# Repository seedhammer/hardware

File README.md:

# SeedHammer II hardware

This repository contains the design files for the [SeedHammer II](https://seedhammer.com)
machine.

## PCB

The schematic and PCB are in [KiCad](https://kicad.org) format. 

Generate production files (gerber, BOM, CPL) with the Go script:
```sh
$ cd pcb
$ PATH=$PATH:/path/to/kicad-cli go run .
```

Production boards are manufactured by [JLCPCB](https://jlcpcb.com) with the following
settings:

 - Surface Finish: ENIG
 - Material Type: FR4 TG155
 - Stackup: JLC04161H-7628 (impedance controlled)

### LCD

The LCD is a [ER-TFT035IPS-6](https://www.buydisplay.com/3-5-inch-ips-320x480-tft-lcd-display-capacitive-touch-screen)
with capacitive touch from buydisplay.com. The variant with resistive touch is not supported by the firmware.

## CAD

The CAD files for the custom machine parts are in STEP format.

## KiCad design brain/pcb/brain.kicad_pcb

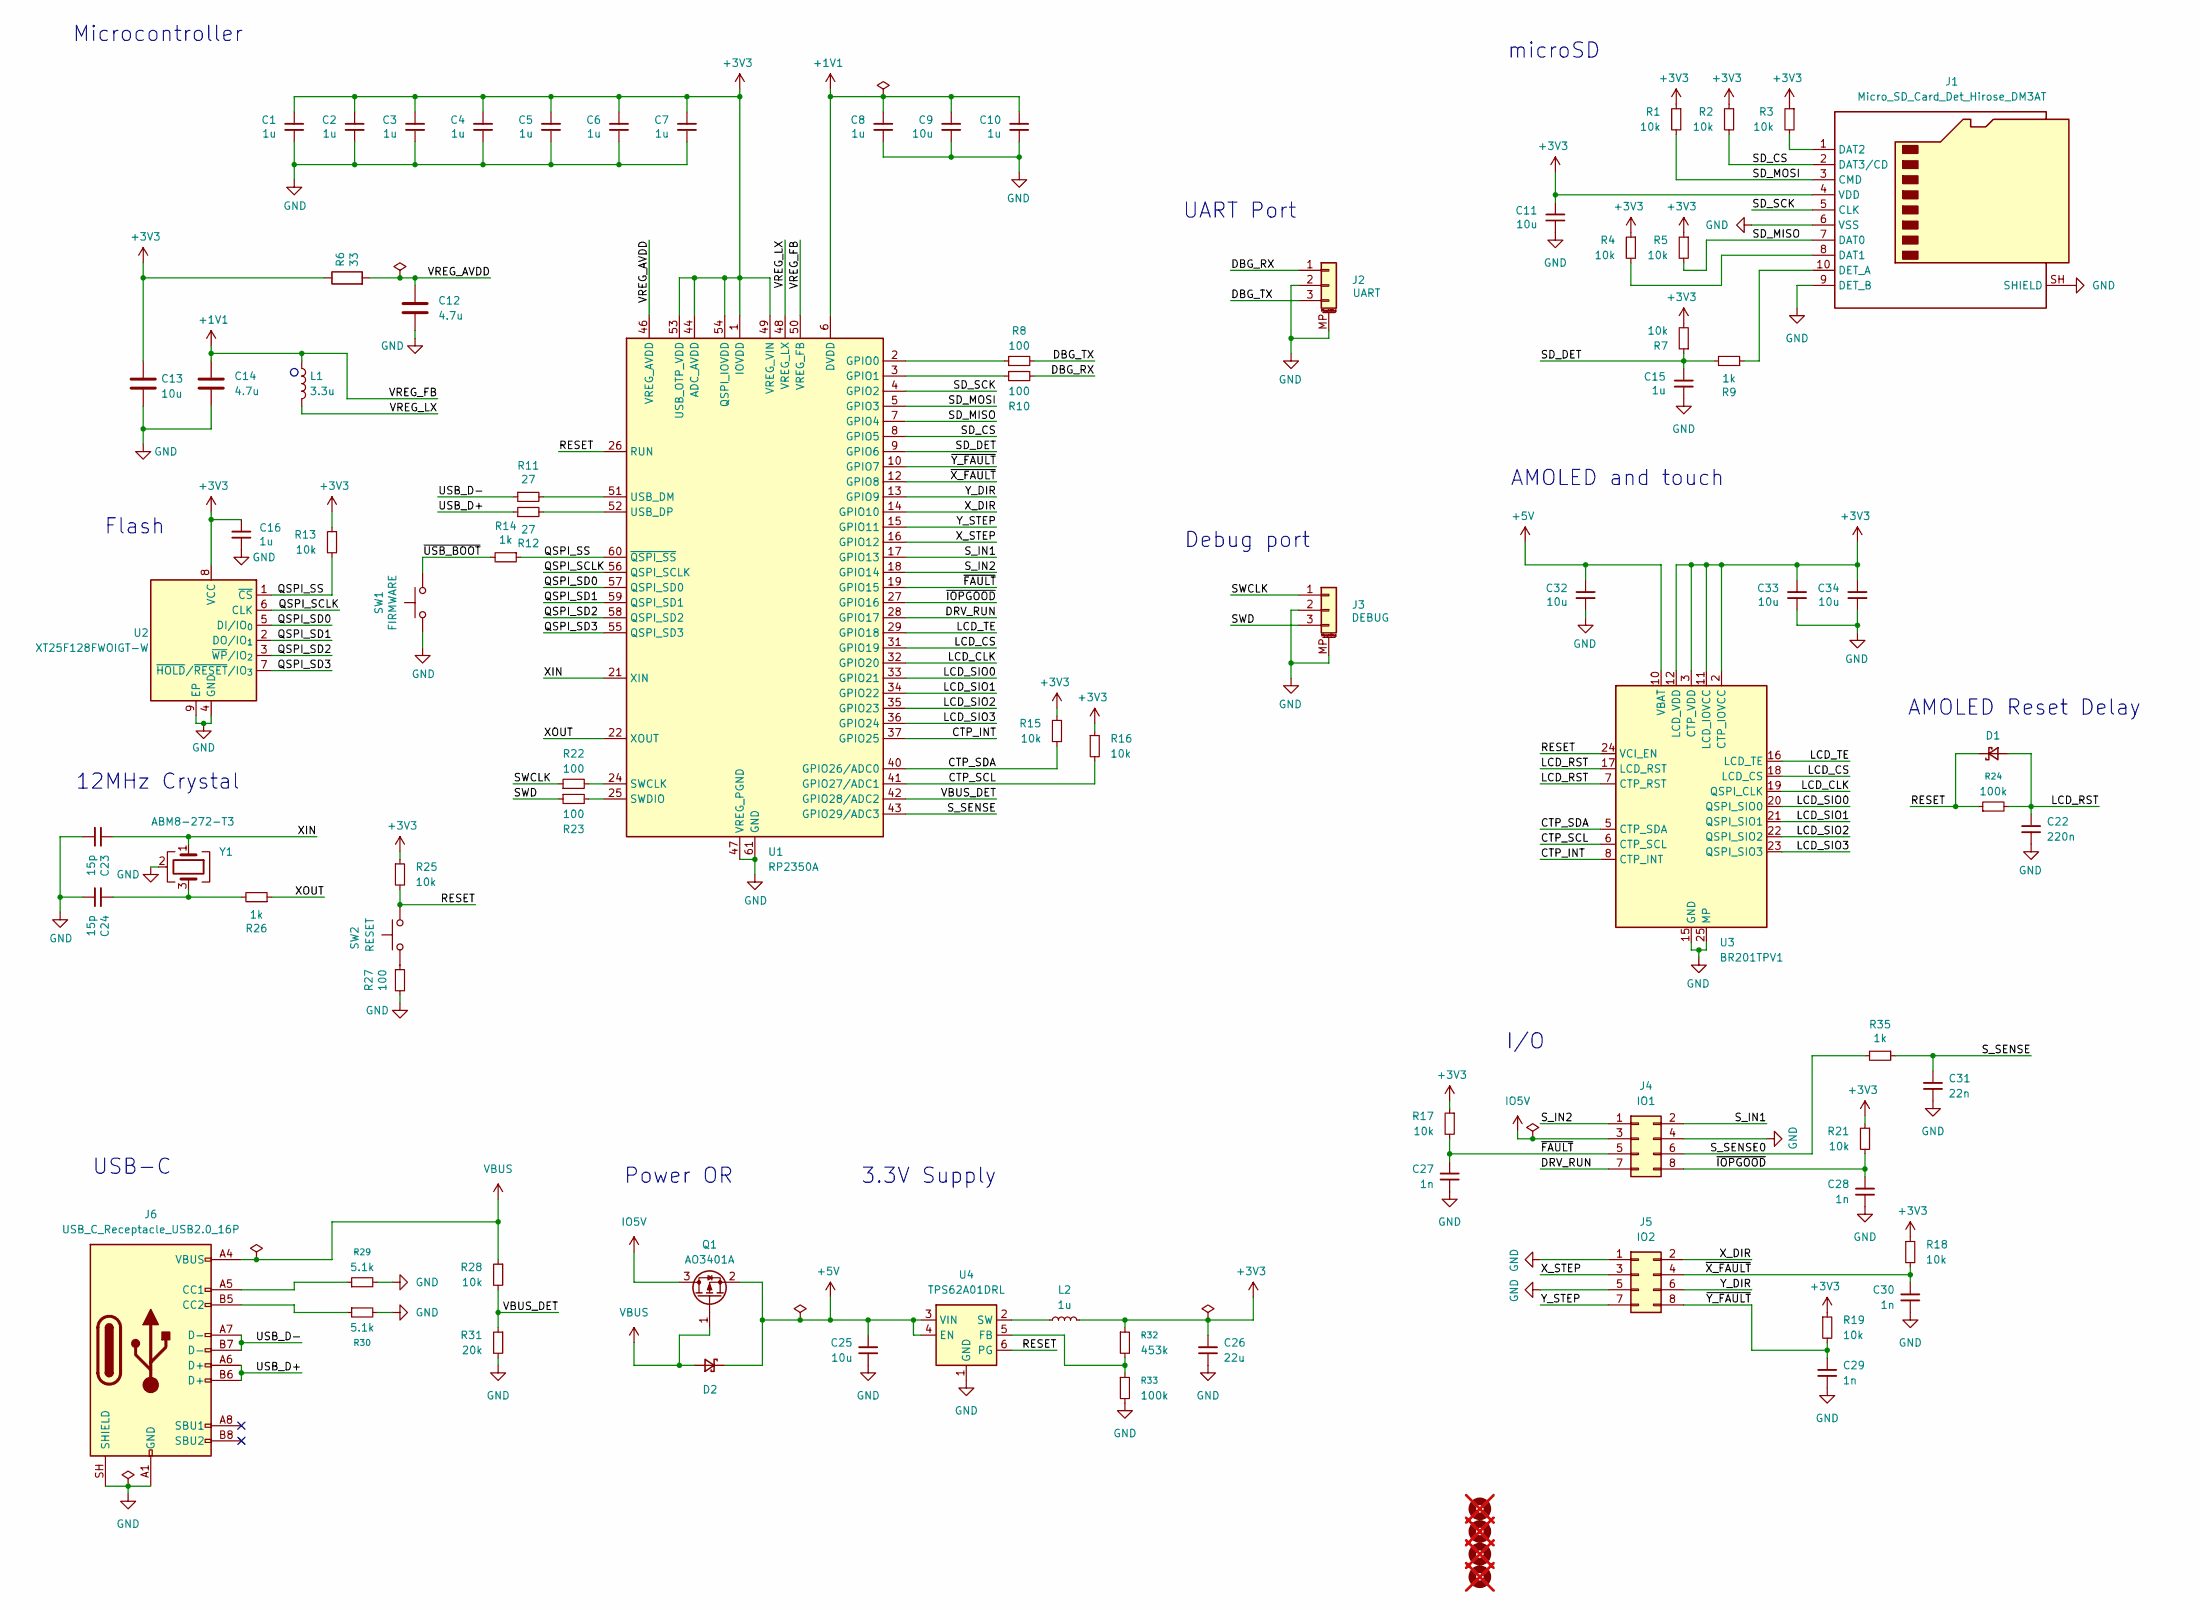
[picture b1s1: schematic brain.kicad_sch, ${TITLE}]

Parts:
C1, C2, C3, C4, C5, C6, C7, C8, C10, C15, C16: 1u; C_0402_1005Metric; LCSC C52923
C9, C11, C32, C33, C34: 10u; C_0402_1005Metric; LCSC C15525
C12: 4.7u; C_0402_1005Metric; LCSC C23733
C13: 10u; C_0402_1005Metric_small_pads; LCSC C15525
C14: 4.7u; C_0402_1005Metric_small_pads; LCSC C23733
C22: 220n; C_0402_1005Metric; LCSC C16772
C23, C24: 15p; C_0402_1005Metric; LCSC C1548
C25: 10u; C_0603_1608Metric; LCSC C96446
C26: 22u; C_0603_1608Metric; LCSC C59461
C27, C28, C29, C30: 1n; C_0402_1005Metric; LCSC C1523
C31: 22n; C_0402_1005Metric; LCSC C1532
D1: D_SOD-523; LCSC C7502700
D2: D_SOD-323; LCSC C191023
H1, H2, H3, H4: MountingHole; MountingHole_2.2mm_M2_DIN965; not fitted
J1: Micro_SD_Card_Det_Hirose_DM3AT; microSD_HC_Hirose_DM3AT-SF-PEJM5; LCSC C114218
J2, J3: WAFER-SH1.0-3PWB; JST_SH_SM03B-SRSS-TB_1x03-1MP_P1.00mm_Horizontal; LCSC C3029342
J4: IO1; Pogo_IO_2x04_P2.5mm
J5: IO2; Pogo_IO_2x04_P2.5mm
J6: USB_C_Receptacle_USB2.0_16P; USB_C_Receptacle_GCT_USB4105-xx-A_16P_TopMnt_Horizontal; LCSC C3020560
L1: 3.3u; L_pol_2016; LCSC C42411119
L2: 1u; L_0603_1608Metric; LCSC C17701610
Q1: AO3401A; SOT-23; LCSC C15127
R1, R2, R3, R4, R5, R7, R13, R15, R16, R17, R18, R19, R21, R25, R28: 10k; R_0402_1005Metric; LCSC C25744
R6: 33; R_0402_1005Metric; LCSC C25105
R8, R10, R22, R23, R27: 100; R_0402_1005Metric; LCSC C25076
R9, R14, R26, R35: 1k; R_0402_1005Metric; LCSC C11702
R11, R12: 27; R_0402_1005Metric; LCSC C2909343
R24, R33: 100k; R_0402_1005Metric; LCSC C25741
R29, R30: 5.1k; R_0402_1005Metric; LCSC C25905
R31: 20k; R_0402_1005Metric; LCSC C25765
R32: 453k; R_0402_1005Metric; LCSC C27009
SW1: TS3425BA; SW_Push_1P1T_NO_Vertical_Wuerth_434133025816; LCSC C2681476
SW2: GT-TC041B-H036-L1N; Panasonic_EVQPUL_EVQPUC; LCSC C2686893
U1: RP2350A; QFN-60-1EP_7x7mm_P0.4mm_EP3.4x3.4mm_ThermalVias; LCSC C42411118
U2: XT25F128FWOIGT-W; WSON-8-1EP_6x5mm_P1.27mm_EP3.4x4mm; LCSC C3202839
U3: BR201TPV1; JMEconn-5014-F024-04-2x12-P05mm; LCSC C55539546
U4: TPS62A01DRL; SOT-563; LCSC C5157937
Y1: ABM8-272-T3; Crystal_SMD_3225-4Pin_3.2x2.5mm; LCSC C20625731

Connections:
+1V1: C8.1, C9.1, C10.1, C14.1, L1.1, U1.6 (DVDD), U1.23 (DVDD), U1.39 (DVDD), U1.50 (VREG_FB)
+3V3: C1.1, C2.1, C3.1, C4.1, C5.1, C6.1, C7.1, C11.1, C13.1, C16.1, C26.1, C33.1, C34.1, J1.4 (VDD), L2.2, R1.1, R2.1, R3.1, R4.1, R5.1, R6.1, R7.2, R13.1, R15.1, R16.1, R17.1, R18.1, R19.1, R21.1, R25.1, R32.1, U1.1 (IOVDD), U1.11 (IOVDD), U1.20 (IOVDD), U1.30 (IOVDD), U1.38 (IOVDD), U1.44 (ADC_AVDD), U1.45 (IOVDD), U1.49 (VREG_VIN), U1.53 (USB_OTP_VDD), U1.54 (QSPI_IOVDD), U2.8 (VCC), U3.2 (CTP_IOVCC), U3.3 (CTP_VDD), U3.11 (LCD_IOVCC), U3.12 (LCD_VDD)
+5V: C25.1, C32.1, D2.1 (K), Q1.2 (S), U3.10 (VBAT), U4.3 (VIN), U4.4 (EN)
/CTP_INT: U1.37 (GPIO25), U3.8 (CTP_INT)
/CTP_SCL: R16.2, U1.41 (GPIO27/ADC1), U3.6 (CTP_SCL)
/CTP_SDA: R15.2, U1.40 (GPIO26/ADC0), U3.5 (CTP_SDA)
/DBG_RX: J2.1, R10.2
/DBG_TX: J2.3, R8.2
/DRV_RUN: J4.7, U1.28 (GPIO17)
/LCD_CLK: U1.32 (GPIO20), U3.19 (QSPI_CLK)
/LCD_CS: U1.31 (GPIO19), U3.18 (LCD_CS)
/LCD_RST: C22.1, D1.2 (A), R24.2, U3.7 (CTP_RST), U3.17 (LCD_RST)
/LCD_SIO0: U1.33 (GPIO21), U3.20 (QSPI_SIO0)
/LCD_SIO1: U1.34 (GPIO22), U3.21 (QSPI_SIO1)
/LCD_SIO2: U1.35 (GPIO23), U3.22 (QSPI_SIO2)
/LCD_SIO3: U1.36 (GPIO24), U3.23 (QSPI_SIO3)
/LCD_TE: U1.29 (GPIO18), U3.16 (LCD_TE)
/QSPI_SCLK: U1.56 (QSPI_SCLK), U2.6 (CLK)
/QSPI_SD0: U1.57 (QSPI_SD0), U2.5 (DI/IO_{0})
/QSPI_SD1: U1.59 (QSPI_SD1), U2.2 (DO/IO_{1})
/QSPI_SD2: U1.58 (QSPI_SD2), U2.3 (~WP/IO_{2})
/QSPI_SD3: U1.55 (QSPI_SD3), U2.7 (~HOLD/~RESET/IO_{3})
/QSPI_SS: R13.2, R14.1, U1.60 (~QSPI_SS), U2.1 (~CS)
/RESET: D1.1 (K), R24.1, R25.2, SW2.1, U1.26 (RUN), U3.24 (VCI_EN), U4.6 (PG)
/SD_CS: J1.2 (DAT3/CD), R2.2, U1.8 (GPIO5)
/SD_DET: C15.1, R7.1, R9.2, U1.9 (GPIO6)
/SD_MISO: J1.7 (DAT0), R5.2, U1.7 (GPIO4)
/SD_MOSI: J1.3 (CMD), R1.2, U1.5 (GPIO3)
/SD_SCK: J1.5 (CLK), U1.4 (GPIO2)
/SWCLK: J3.1, R22.1
/SWD: J3.3, R23.1
/S_IN1: J4.2, U1.17 (GPIO13)
/S_IN2: J4.1, U1.18 (GPIO14)
/S_SENSE: C31.1, R35.1, U1.43 (GPIO29/ADC3)
/S_SENSE0: J4.6, R35.2
/USB_D+: J6.A6 (D+), J6.B6 (D+), R12.1
/USB_D-: J6.A7 (D-), J6.B7 (D-), R11.1
/VBUS_DET: R28.2, R31.1, U1.42 (GPIO28/ADC2)
/VREG_AVDD: C12.1, R6.2, U1.46 (VREG_AVDD)
/VREG_LX: L1.2, U1.48 (VREG_LX)
/XIN: C23.1, U1.21 (XIN), Y1.1
/XOUT: R26.1, U1.22 (XOUT)
/X_DIR: J5.2, U1.14 (GPIO10)
/X_STEP: J5.3, U1.16 (GPIO12)
/Y_DIR: J5.6, U1.13 (GPIO9)
/Y_STEP: J5.7, U1.15 (GPIO11)
/~FAULT: C27.1, J4.5, R17.2, U1.19 (GPIO15)
/~IOPGOOD: C28.1, J4.8, R21.2, U1.27 (GPIO16)
/~USB_BOOT: R14.2, SW1.1
/~X_FAULT: C30.1, J5.4, R18.2, U1.12 (GPIO8)
/~Y_FAULT: C29.1, J5.8, R19.2, U1.10 (GPIO7)
GND: C1.2, C2.2, C3.2, C4.2, C5.2, C6.2, C7.2, C8.2, C9.2, C10.2, C11.2, C12.2, C13.2, C14.2, C15.2, C16.2, C22.2, C23.2, C24.2, C25.2, C26.2, C27.2, C28.2, C29.2, C30.2, C31.2, C32.2, C33.2, C34.2, J1.6 (VSS), J1.9 (DET_B), J1.SH (SHIELD), J2.2, J2.MP (MountPin), J3.2, J3.MP (MountPin), J4.4, J5.1, J5.5, J6.A1 (GND), J6.A12 (GND), J6.B1 (GND), J6.B12 (GND), J6.SH (SHIELD), R27.2, R29.2, R30.2, R31.2, R33.2, SW1.2, U1.47 (VREG_PGND), U1.61 (GND), U2.4 (GND), U2.9 (EP), U3.4 (GND), U3.9 (GND), U3.15 (GND), U3.25 (MP), U3.26 (MP), U3.27 (MP), U3.28 (MP), U4.1 (GND), Y1.2 (G), Y1.4 (G)
IO5V: J4.3, Q1.3 (D)
unnamed: C24.1, R26.2, Y1.3
unnamed: J1.8 (DAT1), R4.2
unnamed: J1.1 (DAT2), R3.2
unnamed: J1.10 (DET_A), R9.1
unnamed: J6.A5 (CC1), R29.1
unnamed: J6.B5 (CC2), R30.1
unnamed: R27.1, SW2.2
unnamed: R8.1, U1.2 (GPIO0)
unnamed: R10.1, U1.3 (GPIO1)
unnamed: R22.2, U1.24 (SWCLK)
unnamed: R23.2, U1.25 (SWDIO)
unnamed: R11.2, U1.51 (USB_DM)
unnamed: R12.2, U1.52 (USB_DP)
unnamed: R32.2, R33.1, U4.5 (FB)
unnamed: L2.1, U4.2 (SW)
VBUS: D2.2 (A), J6.A4 (VBUS), J6.A9 (VBUS), J6.B4 (VBUS), J6.B9 (VBUS), Q1.1 (G), R28.1

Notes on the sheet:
I/O
UART Port
AMOLED Reset Delay
Power OR
USB-C
3.3V Supply
Debug port
microSD
Microcontroller
12MHz Crystal
AMOLED and touch
Flash

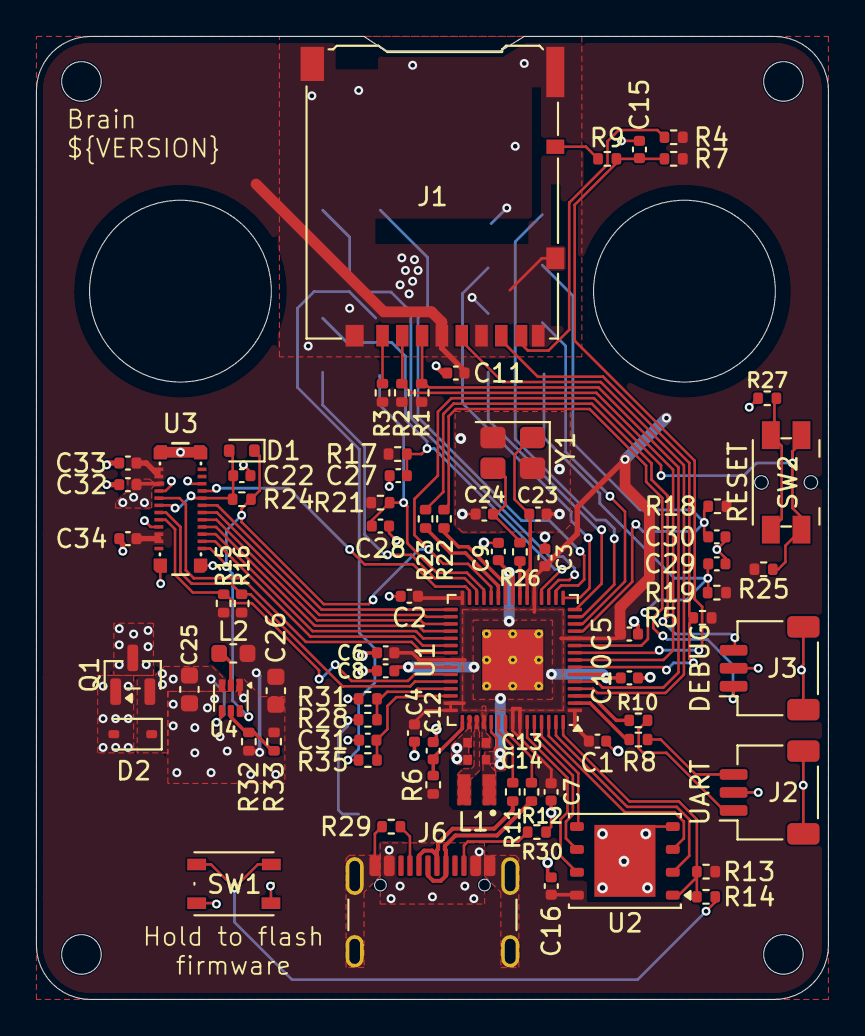
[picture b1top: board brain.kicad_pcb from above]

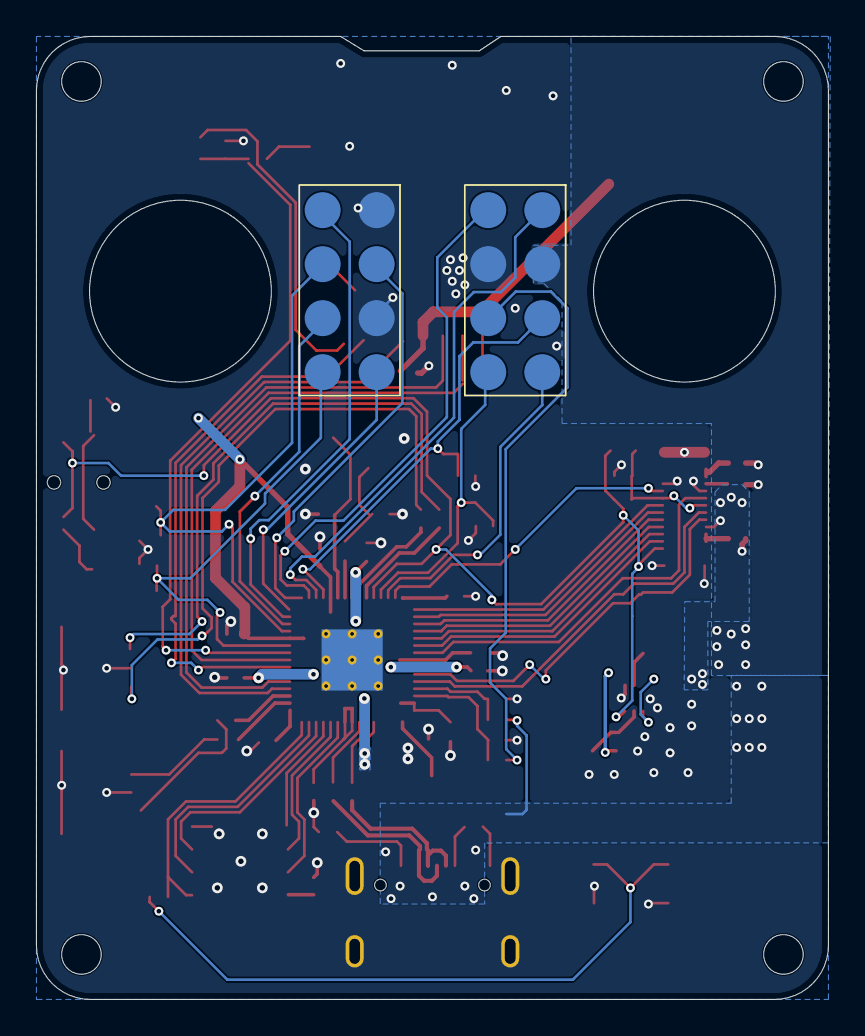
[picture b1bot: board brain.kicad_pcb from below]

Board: 4 copper layers, 44.0 x 53.5 mm, 84 parts (2 on the bottom side), 69 nets.

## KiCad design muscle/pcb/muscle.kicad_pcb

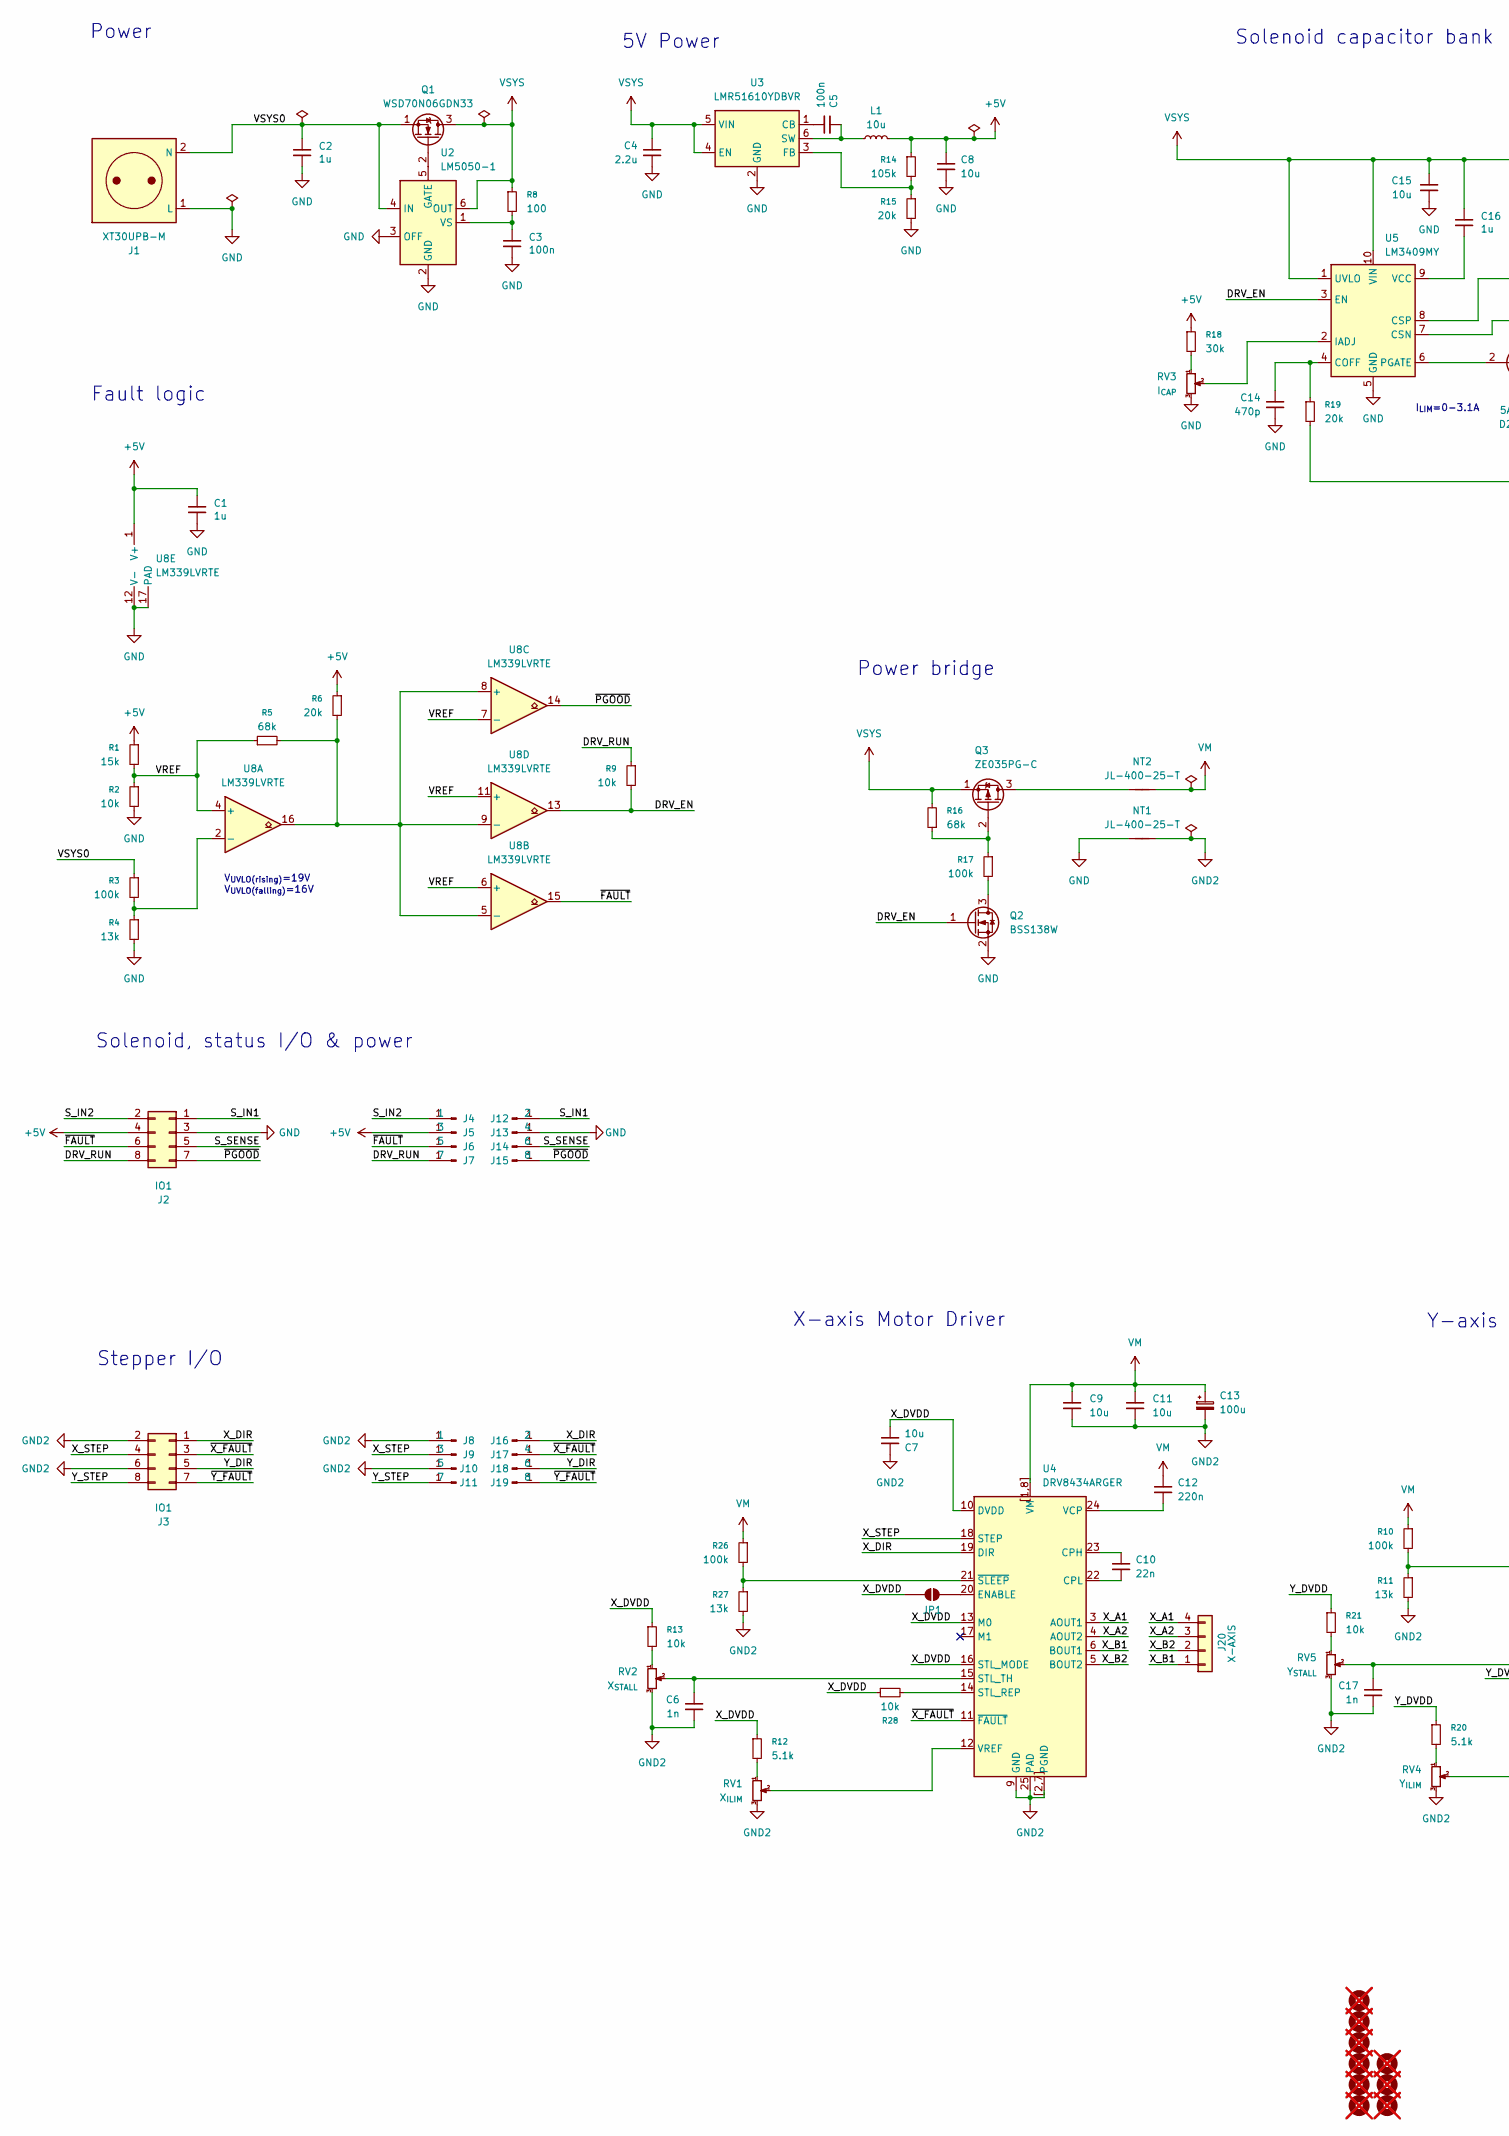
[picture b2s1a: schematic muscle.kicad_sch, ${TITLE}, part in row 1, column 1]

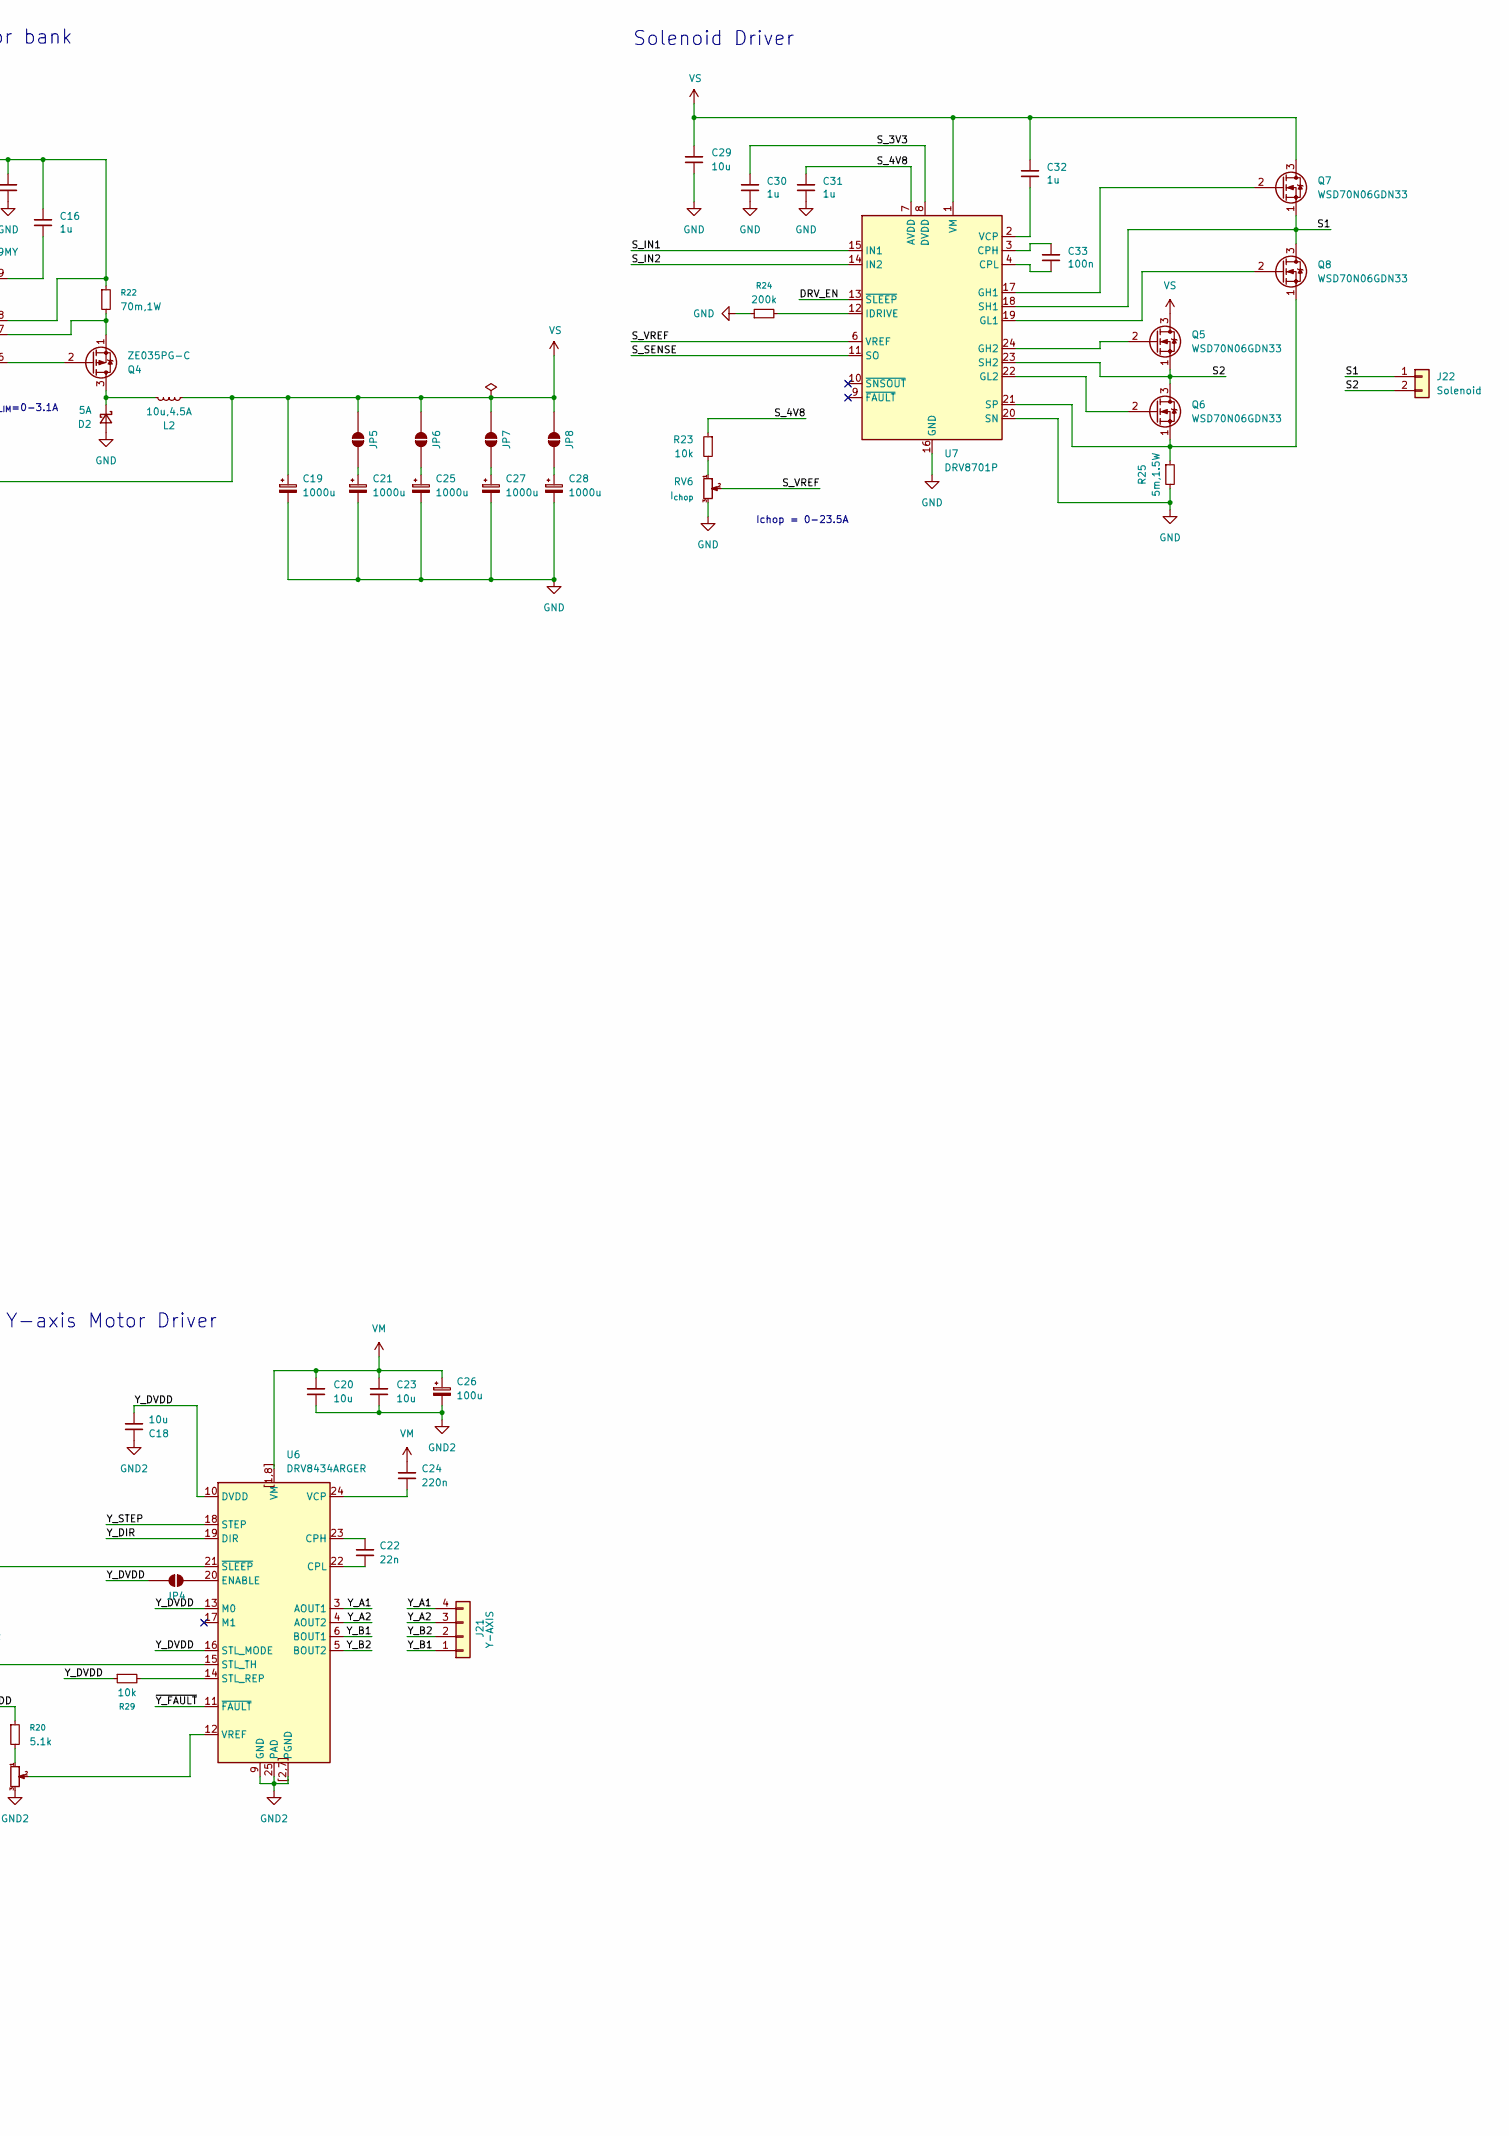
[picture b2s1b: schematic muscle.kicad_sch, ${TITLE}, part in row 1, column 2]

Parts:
C1, C30, C31: 1u; C_0402_1005Metric; LCSC C52923
C2, C16, C32: 1u; C_0603_1608Metric; LCSC C15849
C3, C5, C33: 100n; C_0402_1005Metric; LCSC C307331
C4: 2.2u; C_0805_2012Metric; LCSC C377773
C6, C17: 1n; C_0402_1005Metric; LCSC C1523
C7, C18: 10u; C_0402_1005Metric; LCSC C15525
C8: 10u; C_0603_1608Metric; LCSC C96446
C9, C11, C15, C20, C23, C29: 10u; C_0805_2012Metric; LCSC C440198
C10, C22: 22n; C_0402_1005Metric; LCSC C1532
C12, C24: 220n; C_0402_1005Metric; LCSC C5159775
C13, C26: 100u; CP_Elec_6.3x7.7; LCSC C46550415
C14: 470p; C_0402_1005Metric; LCSC C701296
C19, C21, C25, C27, C28: 1000u; CP_Radial_D13.0mm_P5.00mm; LCSC C47344169
D2: 5A; D_SMA; LCSC C22452
H1, H2, H3, H4, H5, H6, H7, H8, H9: MountingHole; MountingHole_3.2mm_M3_DIN965; not fitted
J1: XT30UPB-M; DC_Jack_HC-DC-084-2.1-03A_Vertical; LCSC C55122157
J2, J3: IO1; IDC-Header_2x04_P2.54mm_Vertical; LCSC C9135
J4, J8: 1; Pogo_SMD_D2.2mm; LCSC C5221286
J5, J9: 3; Pogo_SMD_D2.2mm; LCSC C5221286
J6, J10: 5; Pogo_SMD_D2.2mm; LCSC C5221286
J7, J11: 7; Pogo_SMD_D2.2mm; LCSC C5221286
J12, J16: 2; Pogo_SMD_D2.2mm; LCSC C5221286
J13, J17: 4; Pogo_SMD_D2.2mm; LCSC C5221286
J14, J18: 6; Pogo_SMD_D2.2mm; LCSC C5221286
J15, J19: 8; Pogo_SMD_D2.2mm; LCSC C5221286
J20: B4B-XH-2(LF)(SN); JST_XH_S4B-XH-A-1_1x04_P2.50mm_Horizontal; LCSC C157925
J21: B4B-XH-2(LF)(SN); JST_XH_B4B-XH-A_1x04_P2.50mm_Vertical; LCSC C144395
J22: Solenoid; JST_VH_S2P-VH_1x02_P3.96mm_Horizontal; LCSC C160355
JP1, JP4, JP5, JP6, JP7, JP8: SolderJumper-2_P1.3mm_Open_Pad1.0x1.5mm
L1: 10u; L_1210_3225Metric; LCSC C39846661
L2: 10u,4.5A; L_Bourns_SRP7028A_7.3x6.6mm; LCSC C167223
NT1, NT2: JL-400-25-T; Jumper_Samtec_jl-400-25-t; LCSC C21869072
Q1, Q5, Q6, Q7, Q8: WSD70N06GDN33; FET_DFN-5-1EP_3x3mm_P0.65mm_EP1.25x2.45mm_ThermalVias; LCSC C52034112
Q2: BSS138W; SOT-323_SC-70; LCSC C28646265
Q3, Q4: ZE035PG-C; FET_DFN-5-1EP_3x3mm_P0.65mm_EP1.25x2.45mm_ThermalVias; LCSC C54796285
R1: 15k; R_0402_1005Metric; LCSC C25756
R2, R9, R13, R21, R23, R28, R29: 10k; R_0402_1005Metric; LCSC C25744
R3, R10, R17, R26: 100k; R_0402_1005Metric; LCSC C25741
R4, R11, R27: 13k; R_0402_1005Metric; LCSC C2909319
R5, R16: 68k; R_0402_1005Metric; LCSC C2909379
R6, R15, R19: 20k; R_0402_1005Metric; LCSC C25765
R8: 100; R_0402_1005Metric; LCSC C25076
R12, R20: 5.1k; R_0402_1005Metric; LCSC C25905
R14: 105k; R_0402_1005Metric; LCSC C2933067
R18: 30k; R_0402_1005Metric; LCSC C25776
R22: 70m,1W; R_1206_3216Metric; LCSC C2988663
R24: 200k; R_0402_1005Metric; LCSC C25764
R25: 5m,1.5W; R_2010_5025Metric; LCSC C912931
RV1: X_{ILIM}; Potentiometer_Bourns_TC33X_Vertical; LCSC C719176
RV2: X_{STALL}; Potentiometer_Bourns_TC33X_Vertical; LCSC C719176
RV3: I_{CAP}; Potentiometer_Bourns_TC33X_Vertical; LCSC C719176
RV4: Y_{ILIM}; Potentiometer_Bourns_TC33X_Vertical; LCSC C719176
RV5: Y_{STALL}; Potentiometer_Bourns_TC33X_Vertical; LCSC C719176
RV6: I_{chop}; Potentiometer_Bourns_TC33X_Vertical; LCSC C719176
U2: LM5050-1; TSOT-23-6; LCSC C473393
U3: LMR51610YDBVR; SOT-23-6; LCSC C22427220
U4, U6: DRV8434ARGER; Texas_RGE0024H_VQFN-24-1EP_4x4mm_P0.5mm_EP2.7x2.7mm_Thermal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; LCSC C2866434
U5: LM3409MY; HVSSOP-10-1EP_3x3mm_P0.5mm_EP1.83x1.89mm_ThermalVias; LCSC C473394
U7: DRV8701P; VQFN-24-1EP_4x4mm_P0.5mm_EP2.45x2.45mm_ThermalVias; LCSC C114178
U8: LM339LVRTE; WQFN-16-1EP_3x3mm_P0.5mm_EP1.68x1.68mm; LCSC C3658606

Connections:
+5V: C1.1, C8.1, J2.4, J5.1 (Pin_1_1), L1.2, R1.1, R6.1, R14.1, R18.1, U8.1 (V+)
/DRV_EN: Q2.1 (G), R9.2, U5.3 (EN), U7.13 (~SLEEP), U8.13
/DRV_RUN: J2.8, J7.1 (Pin_1_1), R9.1
/S1: J22.1, Q7.1 (S), Q8.3 (D), U7.18 (SH1)
/S2: J22.2, Q5.1 (S), Q6.3 (D), U7.23 (SH2)
/S_3V3: C30.1, U7.8 (DVDD)
/S_4V8: C31.1, R23.1, U7.7 (AVDD)
/S_IN1: J2.1, J12.1 (Pin_1_1), U7.15 (IN1)
/S_IN2: J2.2, J4.1 (Pin_1_1), U7.14 (IN2)
/S_SENSE: J2.5, J14.1 (Pin_1_1), U7.11 (SO)
/S_VREF: RV6.2, U7.6 (VREF)
/VREF: R1.2, R2.1, R5.1, U8.4 (+), U8.6 (+), U8.7 (-), U8.11 (+)
/VSYS0: C2.1, J1.2 (N), Q1.1 (S), R3.1, U2.4 (IN)
/X_A1: J20.4, U4.3 (AOUT1)
/X_A2: J20.3, U4.4 (AOUT2)
/X_B1: J20.1, U4.6 (BOUT1)
/X_B2: J20.2, U4.5 (BOUT2)
/X_DIR: J3.1, J16.1 (Pin_1_1), U4.19 (DIR)
/X_DVDD: C7.2, JP1.1 (A), R12.1, R13.1, R28.1, U4.10 (DVDD), U4.13 (M0), U4.16 (STL_MODE)
/X_STEP: J3.4, J9.1 (Pin_1_1), U4.18 (STEP)
/Y_A1: J21.4, U6.3 (AOUT1)
/Y_A2: J21.3, U6.4 (AOUT2)
/Y_B1: J21.1, U6.6 (BOUT1)
/Y_B2: J21.2, U6.5 (BOUT2)
/Y_DIR: J3.5, J18.1 (Pin_1_1), U6.19 (DIR)
/Y_DVDD: C18.2, JP4.1 (A), R20.1, R21.1, R29.1, U6.10 (DVDD), U6.13 (M0), U6.16 (STL_MODE)
/Y_STEP: J3.8, J11.1 (Pin_1_1), U6.18 (STEP)
/~FAULT: J2.6, J6.1 (Pin_1_1), U8.15
/~PGOOD: J2.7, J15.1 (Pin_1_1), U8.14
/~X_FAULT: J3.3, J17.1 (Pin_1_1), U4.11 (~FAULT)
/~Y_FAULT: J3.7, J19.1 (Pin_1_1), U6.11 (~FAULT)
GND: C1.2, C2.2, C3.2, C4.2, C8.2, C14.2, C15.2, C19.2, C21.2, C25.2, C27.2, C28.2, C29.2, C30.2, C31.2, D2.2 (A), J1.1 (L), J2.3, J13.1 (Pin_1_1), NT1.1, Q2.2 (S), R2.2, R4.2, R15.2, R24.1, R25.2, RV3.3, RV6.3, U2.2 (GND), U2.3 (OFF), U3.2 (GND), U5.5 (GND), U5.11 (PAD), U7.5 (GND), U7.16 (GND), U7.20 (SN), U7.25 (GND), U8.12 (V-), U8.17 (PAD)
GND2: C6.2, C7.1, C9.2, C11.2, C13.2, C17.2, C18.1, C20.2, C23.2, C26.2, J3.2, J3.6, J8.1 (Pin_1_1), J10.1 (Pin_1_1), NT1.2, R11.2, R27.2, RV1.3, RV2.3, RV4.3, RV5.3, U4.2 (PGND), U4.7 (PGND), U4.9 (GND), U4.25 (PAD), U4.[2,7] (PGND), U6.2 (PGND), U6.7 (PGND), U6.9 (GND), U6.25 (PAD), U6.[2,7] (PGND)
unnamed: D2.1 (K), L2.1, Q4.3 (D)
unnamed: JP1.2 (B), U4.20 (ENABLE)
unnamed: JP4.2 (B), U6.20 (ENABLE)
unnamed: C21.1, JP5.1 (A)
unnamed: C25.1, JP6.1 (A)
unnamed: C27.1, JP7.1 (A)
unnamed: C28.1, JP8.1 (A)
unnamed: Q1.2 (G), U2.5 (GATE)
unnamed: Q2.3 (D), R17.2
unnamed: NT2.1, Q3.3 (D)
unnamed: Q3.2 (G), R16.1, R17.1
unnamed: Q4.2 (G), U5.6 (PGATE)
unnamed: Q4.1 (S), R22.2, U5.7 (CSN)
unnamed: Q5.2 (G), U7.24 (GH2)
unnamed: Q6.2 (G), U7.22 (GL2)
unnamed: Q6.1 (S), Q8.1 (S), R25.1, U7.21 (SP)
unnamed: Q7.2 (G), U7.17 (GH1)
unnamed: Q8.2 (G), U7.19 (GL1)
unnamed: R12.2, RV1.1
unnamed: R13.2, RV2.1
unnamed: R18.2, RV3.1
unnamed: R20.2, RV4.1
unnamed: R21.2, RV5.1
unnamed: R23.2, RV6.1
unnamed: C3.1, R8.2, U2.1 (VS)
unnamed: C5.2, U3.1 (CB)
unnamed: R14.2, R15.1, U3.3 (FB)
unnamed: C5.1, L1.1, U3.6 (SW)
unnamed: C10.1, U4.23 (CPH)
unnamed: C10.2, U4.22 (CPL)
unnamed: R28.2, U4.14 (STL_REP)
unnamed: C6.1, RV2.2, U4.15 (STL_TH)
unnamed: C12.2, U4.24 (VCP)
unnamed: RV1.2, U4.12 (VREF)
unnamed: R26.2, R27.1, U4.21 (~SLEEP)
unnamed: C14.1, R19.1, U5.4 (COFF)
unnamed: RV3.2, U5.2 (IADJ)
unnamed: C16.2, U5.9 (VCC)
unnamed: C22.1, U6.23 (CPH)
unnamed: C22.2, U6.22 (CPL)
unnamed: R29.2, U6.14 (STL_REP)
unnamed: C17.1, RV5.2, U6.15 (STL_TH)
unnamed: C24.2, U6.24 (VCP)
unnamed: RV4.2, U6.12 (VREF)
unnamed: R10.2, R11.1, U6.21 (~SLEEP)
unnamed: C33.1, U7.3 (CPH)
unnamed: C33.2, U7.4 (CPL)
unnamed: R24.2, U7.12 (IDRIVE)
unnamed: C32.2, U7.2 (VCP)
unnamed: R3.2, R4.1, U8.2 (-)
unnamed: R5.2, R6.2, U8.5 (-), U8.8 (+), U8.9 (-), U8.16
VM: C9.1, C11.1, C12.1, C13.1, C20.1, C23.1, C24.1, C26.1, NT2.2, R10.1, R26.1, U4.1 (VM), U4.8 (VM), U4.[1,8] (VM), U6.1 (VM), U6.8 (VM), U6.[1,8] (VM)
VS: C19.1, C29.1, C32.1, JP5.2 (B), JP6.2 (B), JP7.2 (B), JP8.2 (B), L2.2, Q5.3 (D), Q7.3 (D), R19.2, U7.1 (VM)
VSYS: C4.1, C15.1, C16.1, Q1.3 (D), Q3.1 (S), R8.1, R16.2, R22.1, U2.6 (OUT), U3.4 (EN), U3.5 (VIN), U5.1 (UVLO), U5.8 (CSP), U5.10 (VIN)

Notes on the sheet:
Ichop = 0-23.5A
Fault logic
I_{LIM}=0-3.1A
X-axis Motor Driver
Solenoid Driver
5V Power
Y-axis Motor Driver
Power bridge
Solenoid capacitor bank
Stepper I/O
V_{UVLO(rising)}=19V V_{UVLO(falling)}=16V
Solenoid, status I/O & power
Power

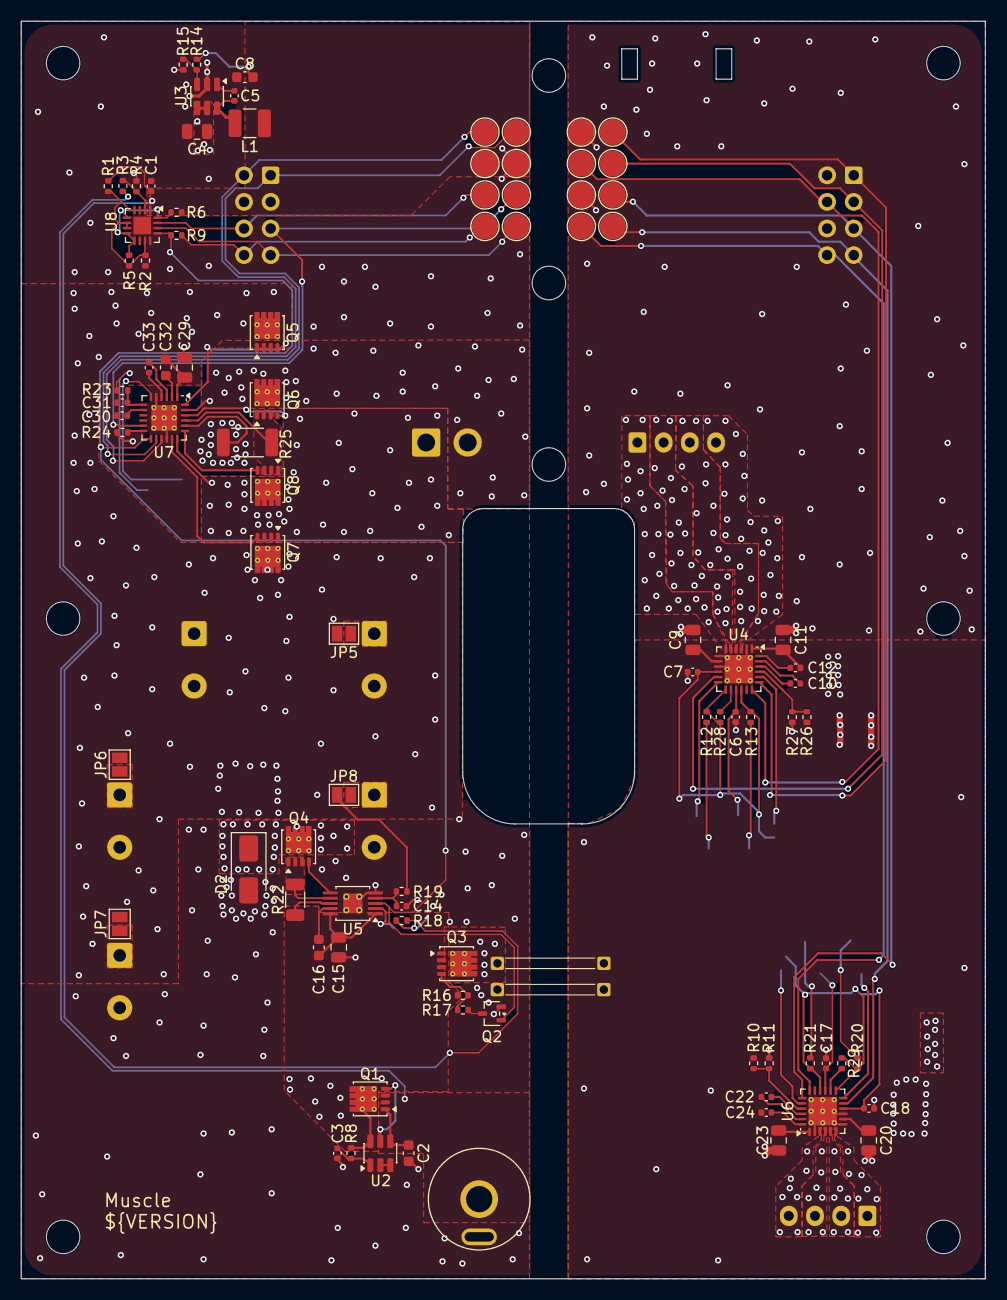
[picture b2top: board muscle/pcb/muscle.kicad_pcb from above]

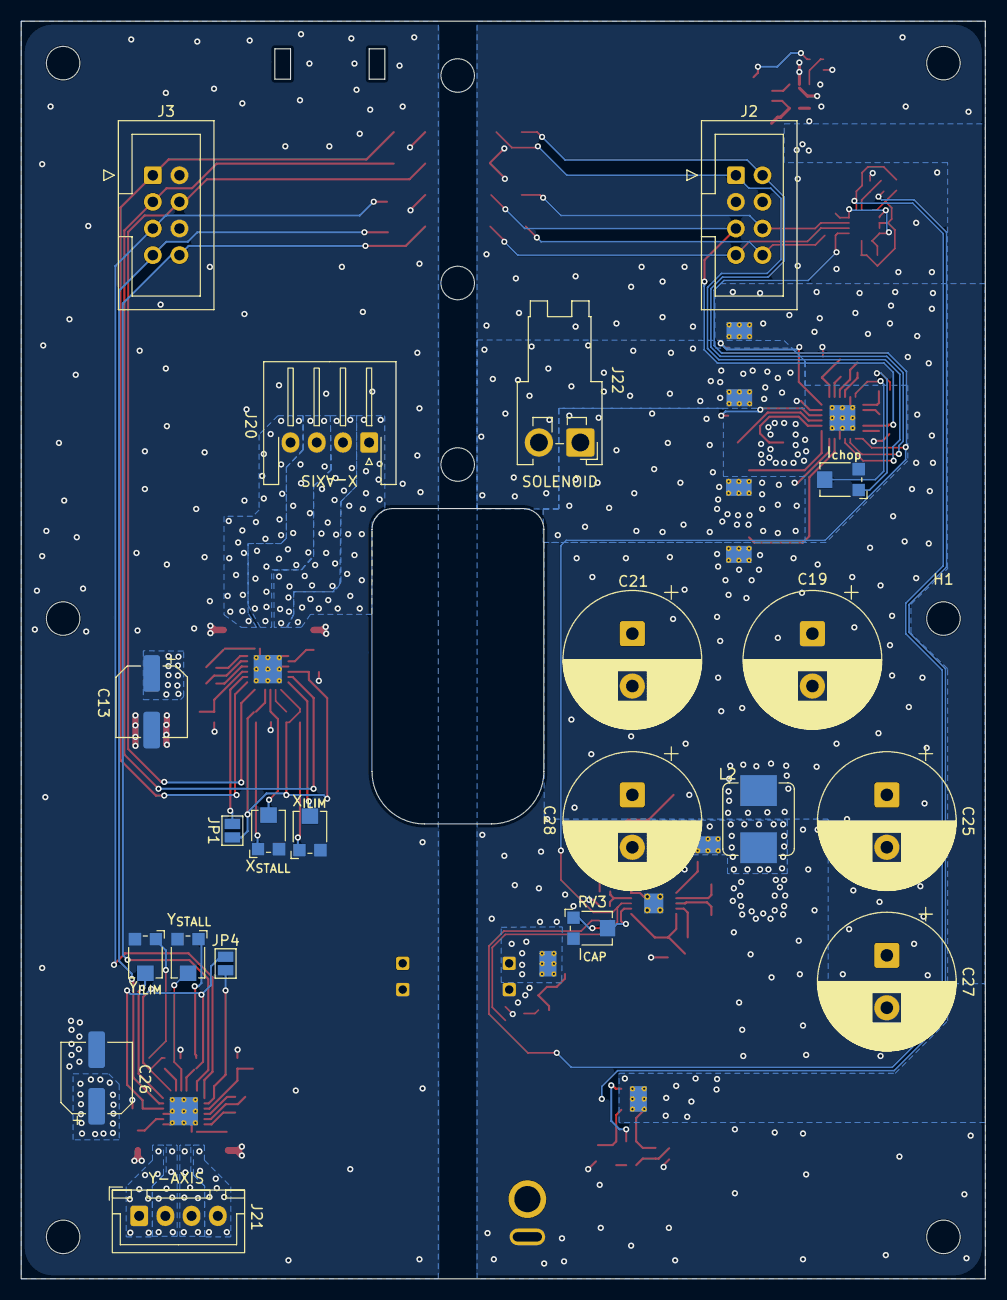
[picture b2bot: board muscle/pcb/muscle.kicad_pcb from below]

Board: 4 copper layers, 92.0 x 120.0 mm, 124 parts (30 on the bottom side), 87 nets.
